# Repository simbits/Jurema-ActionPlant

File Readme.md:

Prototype for a new BioMachine
=====================

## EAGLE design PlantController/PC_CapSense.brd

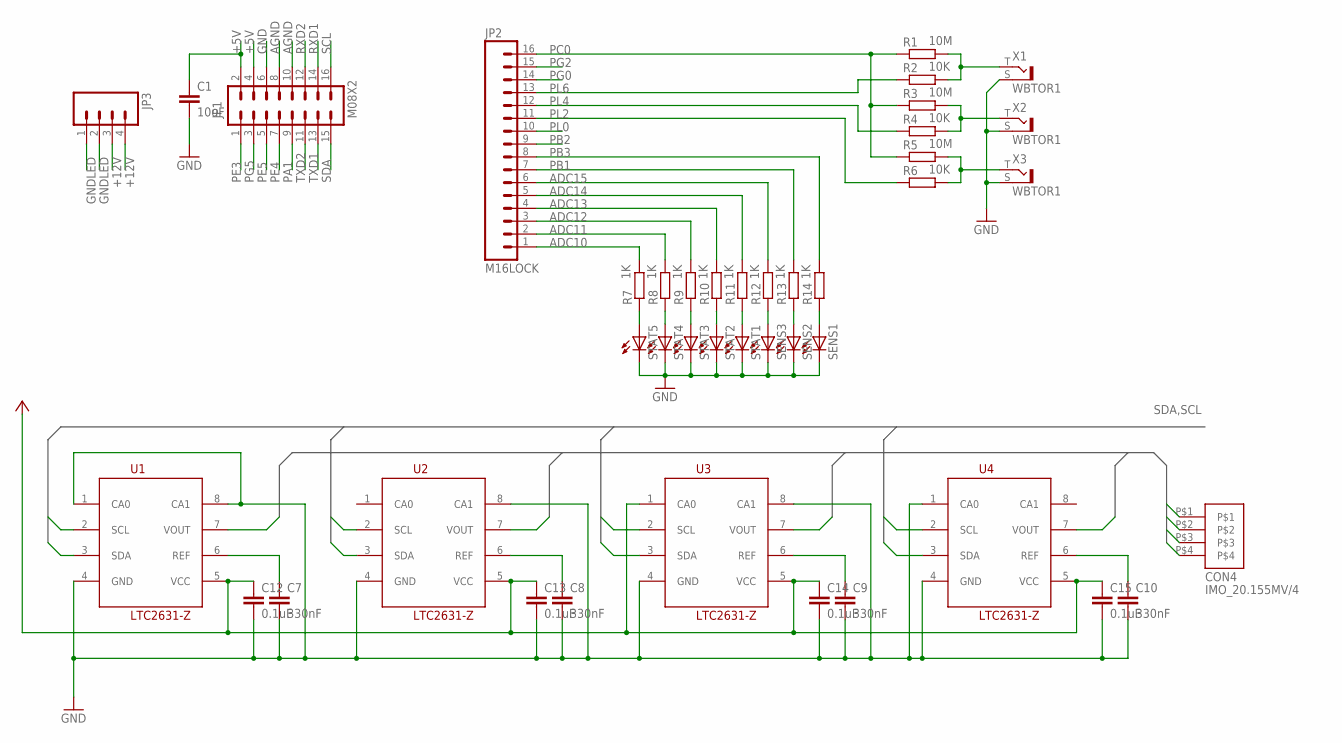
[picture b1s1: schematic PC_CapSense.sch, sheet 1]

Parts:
C1: 10uF; C0805
C7, C8, C9, C10: 330nF; C0805K
C12, C13, C14, C15: 0.1uF; C0805K
CON4: IMO_20.155MV/4
JP1: M08X2; 2X8
JP2: M16LOCK; 1X16_LOCK
JP3: M04LONGPADS; 1X04_LONGPADS
R1, R3, R5: 10M; M0805
R2, R4, R6: 10K; M0805
R7, R8, R9, R10, R11, R12, R13, R14: 1K; M0805
SENS1, SENS2, SENS3: LED3MM
STAT1, STAT2, STAT3, STAT4, STAT5: LED3MM
U1, U2, U3, U4: LTC2631-Z; TSOT23-8
X1, X2, X3: WBTOR1

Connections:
+5V: C1.1, C12.1, C13.1, C14.1, C15.1, JP1.2, JP1.4, U1.5 (VCC), U2.5 (VCC), U3.1 (CA0), U3.5 (VCC), U4.5 (VCC)
+12V: JP3.3, JP3.4
ADC10: JP2.1, R7.2
ADC11: JP2.2, R8.2
ADC12: JP2.3, R9.2
ADC13: JP2.4, R10.2
ADC14: JP2.5, R11.2
ADC15: JP2.6, R12.2
AGND: JP1.8, JP1.10, X1.S, X2.S, X3.S
GND: C1.2, C7.2, C8.2, C9.2, C10.2, C12.2, C13.2, C14.2, C15.2, JP1.6, U1.1 (CA0), U1.4 (GND), U1.8 (CA1), U2.4 (GND), U2.8 (CA1), U3.4 (GND), U3.8 (CA1), U4.1 (CA0), U4.4 (GND)
GNDLED: JP3.1, JP3.2, SENS1.K (C), SENS2.K (C), SENS3.K (C), STAT1.K (C), STAT2.K (C), STAT3.K (C), STAT4.K (C), STAT5.K (C)
unnamed: R1.2, R2.2, X1.T
unnamed: R3.2, R4.2, X2.T
unnamed: R5.2, R6.2, X3.T
unnamed: R7.1, STAT5.A
unnamed: R8.1, STAT4.A
unnamed: R9.1, STAT3.A
unnamed: R10.1, STAT2.A
unnamed: R11.1, STAT1.A
unnamed: R12.1, SENS3.A
unnamed: R13.1, SENS2.A
unnamed: R14.1, SENS1.A
unnamed: C10.1, U4.6 (REF)
unnamed: C9.1, U3.6 (REF)
unnamed: C8.1, U2.6 (REF)
unnamed: C7.1, U1.6 (REF)
PA1: JP1.9
PB1: JP2.7, R13.2
PB2: JP2.9
PB3: JP2.8, R14.2
PC0: JP2.16, R1.1, R3.1, R5.1
PE3: JP1.1
PE4: JP1.7
PE5: JP1.5
PG0: JP2.14
PG2: JP2.15
PG5: JP1.3
PL0: JP2.10
PL2: JP2.11, R6.1
PL4: JP2.12, R4.1
PL6: JP2.13, R2.1
RXD1: JP1.14
RXD2: JP1.12
SCL: JP1.16, U1.2 (SCL), U2.2 (SCL), U3.2 (SCL), U4.2 (SCL)
SDA: JP1.15, U1.3 (SDA), U2.3 (SDA), U3.3 (SDA), U4.3 (SDA)
TXD1: JP1.13
TXD2: JP1.11
VOUT0: CON4.P$1, U1.7 (VOUT)
VOUT1: CON4.P$2, U2.7 (VOUT)
VOUT2: CON4.P$3, U3.7 (VOUT)
VOUT3: CON4.P$4, U4.7 (VOUT)

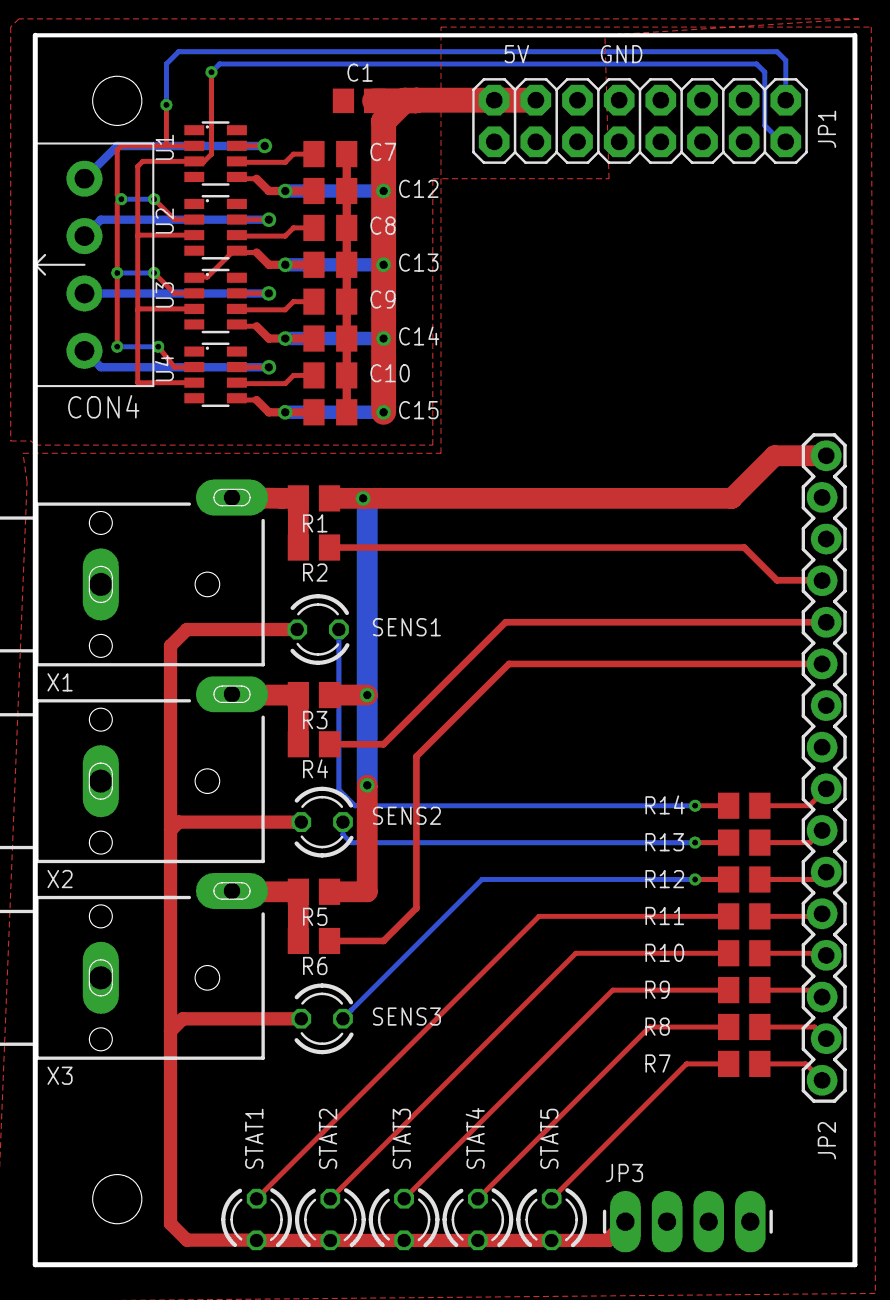
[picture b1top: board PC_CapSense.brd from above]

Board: 2 copper layers, 50.0 x 75.0 mm, 42 parts (0 on the bottom side), 38 nets.

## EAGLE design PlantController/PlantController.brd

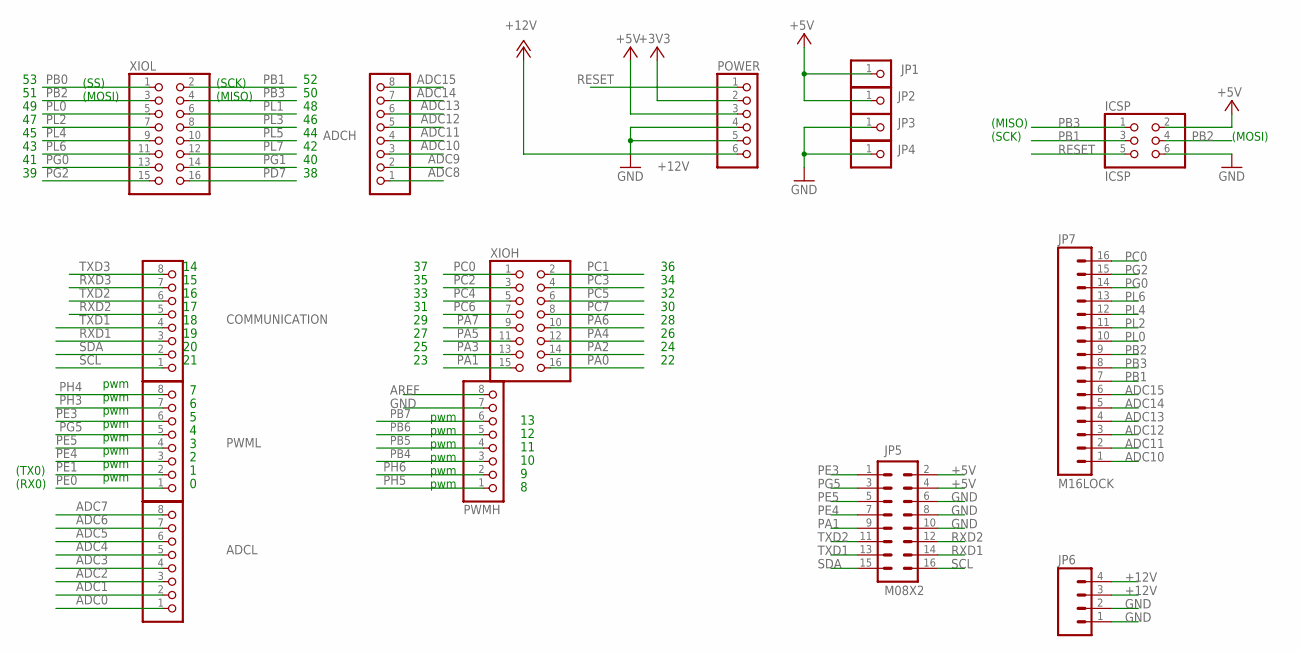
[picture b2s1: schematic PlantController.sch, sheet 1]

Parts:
ADCH: PINHD-1X8; 1X08
ADCL: PINHD-1X8; 1X08
COMMUNICATION: PINHD-1X8; 1X08
ICSP: ICSP; 2X03
JP1, JP2, JP3, JP4: PINHD-1X1; 1X01
JP5: M08X2; 2X8
JP6: M04LONGPADS; 1X04_LONGPADS
JP7: M16LOCK; 1X16_LOCK
POWER: PINHD-1X6; 1X06
PWMH: PINHD-1X8; 1X08
PWML: PINHD-1X8; 1X08
XIOH: PINHD-2X8; 2X08
XIOL: PINHD-2X8; 2X08

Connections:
+3V3: POWER.2
+5V: ICSP.2, JP1.1, JP2.1, JP5.2, JP5.4, POWER.3
+12V: JP6.3, JP6.4, POWER.6; also elsewhere on the board
ADC0: ADCL.1; also elsewhere on the board
ADC1: ADCL.2; also elsewhere on the board
ADC2: ADCL.3; also elsewhere on the board
ADC3: ADCL.4; also elsewhere on the board
ADC4: ADCL.5
ADC5: ADCL.6
ADC6: ADCL.7
ADC7: ADCL.8
ADC8: ADCH.1
ADC9: ADCH.2
ADC10: ADCH.3, JP7.1
ADC11: ADCH.4, JP7.2
ADC12: ADCH.5, JP7.3
ADC13: ADCH.6, JP7.4
ADC14: ADCH.7, JP7.5
ADC15: ADCH.8, JP7.6
AREF: PWMH.8
GND: ICSP.6, JP3.1, JP4.1, JP5.6, JP5.8, JP5.10, JP6.1, JP6.2, POWER.4, POWER.5, PWMH.7; also elsewhere on the board
PA0: XIOH.16
PA1: JP5.9, XIOH.15
PA2: XIOH.14
PA3: XIOH.13
PA4: XIOH.12
PA5: XIOH.11
PA6: XIOH.10
PA7: XIOH.9
PB0: XIOL.1
PB1: ICSP.3, JP7.7, XIOL.2
PB2: ICSP.4, JP7.9, XIOL.3
PB3: ICSP.1, JP7.8, XIOL.4
PB4: PWMH.3
PB5: PWMH.4
PB6: PWMH.5
PB7: PWMH.6
PC0: JP7.16, XIOH.1
PC1: XIOH.2
PC2: XIOH.3
PC3: XIOH.4
PC4: XIOH.5
PC5: XIOH.6
PC6: XIOH.7
PC7: XIOH.8
PD7: XIOL.16
PE0: PWML.1
PE1: PWML.2
PE3: JP5.1, PWML.6
PE4: JP5.7, PWML.3
PE5: JP5.5, PWML.4
PG0: JP7.14, XIOL.13
PG1: XIOL.14
PG2: JP7.15, XIOL.15
PG5: JP5.3, PWML.5
PH3: PWML.7
PH4: PWML.8
PH5: PWMH.1
PH6: PWMH.2
PL0: JP7.10, XIOL.5
PL1: XIOL.6
PL2: JP7.11, XIOL.7
PL3: XIOL.8
PL4: JP7.12, XIOL.9
PL5: XIOL.10
PL6: JP7.13, XIOL.11
PL7: XIOL.12
RESET: ICSP.5, POWER.1
RXD1: COMMUNICATION.3, JP5.14
RXD2: COMMUNICATION.5, JP5.12
RXD3: COMMUNICATION.7
SCL: COMMUNICATION.1, JP5.16
SDA: COMMUNICATION.2, JP5.15
TXD1: COMMUNICATION.4, JP5.13
TXD2: COMMUNICATION.6, JP5.11
TXD3: COMMUNICATION.8

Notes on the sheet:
(SCK)
(MISO)
(MOSI)
pwm
(TX0)
(RX0)
(SS)

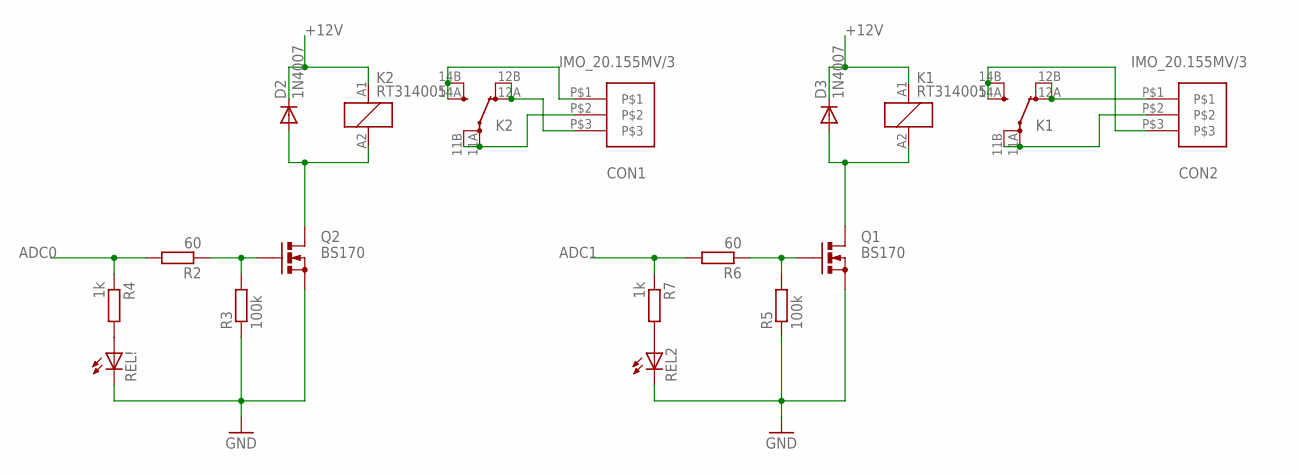
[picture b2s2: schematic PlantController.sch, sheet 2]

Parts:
CON1, CON2: IMO_20.155MV/3
D2, D3: 1N4007; DO41-10
K1, K2: RT314005; RT-C/O16A5
Q1, Q2: BS170; SOT54E
R2, R6: 60; R0805
R3, R5: 100k; R0805
R4, R7: 1k; R0805
REL2: LED5MM
REL!: LED5MM

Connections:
+12V: D2.C, D3.C, K1.A1 (1), K2.A1 (1); also elsewhere on the board
ADC0: R2.2, R4.1; also elsewhere on the board
ADC1: R6.2, R7.1; also elsewhere on the board
GND: Q1.S, Q2.S, R3.1, R5.1, REL2.K (C), REL!.K (C); also elsewhere on the board
unnamed: D2.A, K2.A2 (2), Q2.D
unnamed: Q2.G, R2.1, R3.2
unnamed: D3.A, K1.A2 (2), Q1.D
unnamed: R4.2, REL!.A
unnamed: Q1.G, R5.2, R6.1
unnamed: R7.2, REL2.A
unnamed: CON1.P$2, K2.11A (PA), K2.11B (PB)
unnamed: CON1.P$3, K2.12A (OA), K2.12B (OB)
unnamed: CON1.P$1, K2.14A (SA), K2.14B (SB)
unnamed: CON2.P$2, K1.11A (PA), K1.11B (PB)
unnamed: CON2.P$1, K1.12A (OA), K1.12B (OB)
unnamed: CON2.P$3, K1.14A (SA), K1.14B (SB)

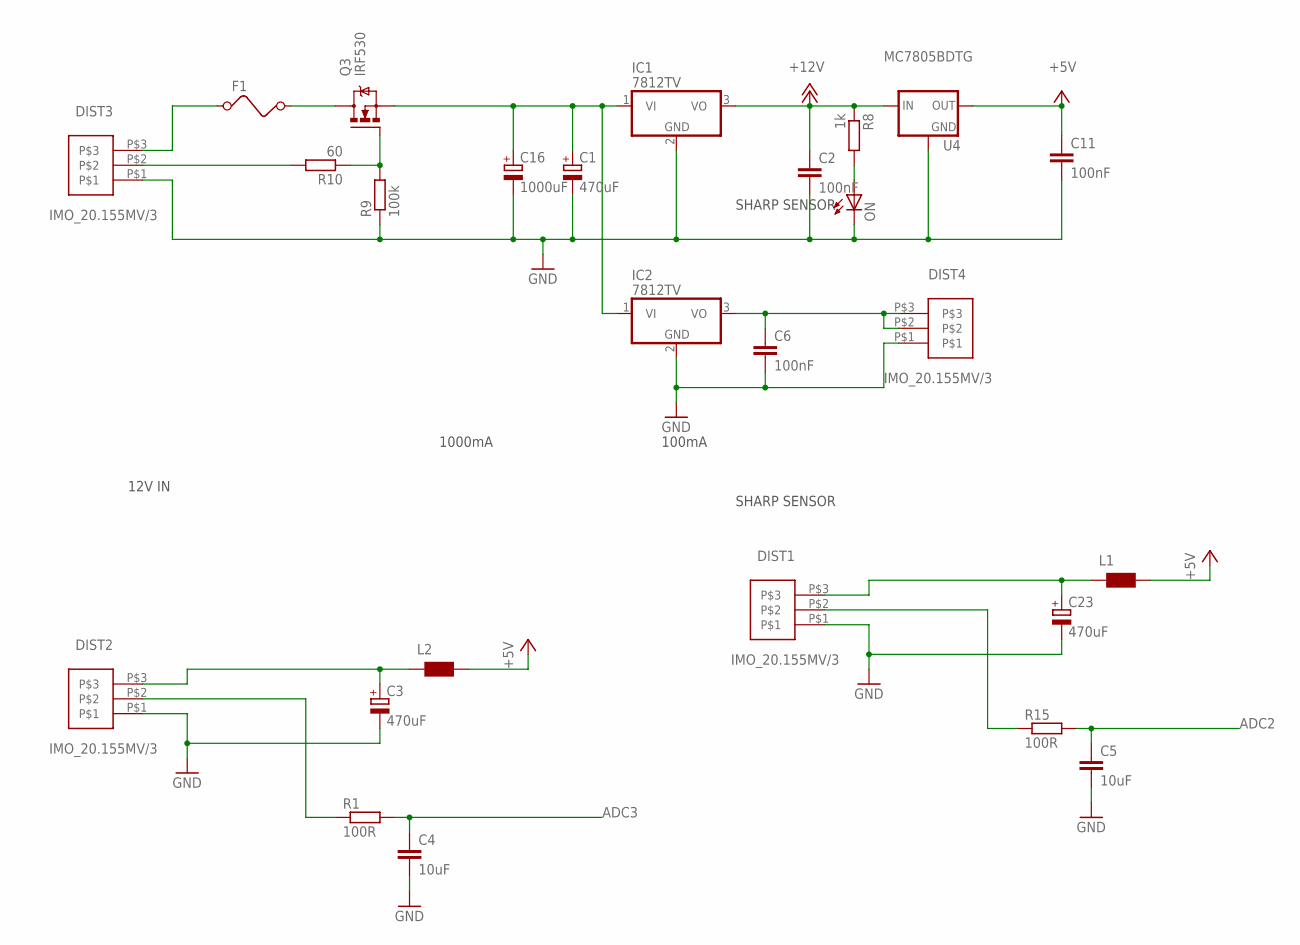
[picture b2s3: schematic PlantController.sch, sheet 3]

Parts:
C1: 470uF; E7,5-16
C2, C6, C11: 100nF; C0805K
C3, C23: 470uF; PANASONIC_F
C4, C5: 10uF; C0805K
C16: 1000uF; E7,5-16
DIST1, DIST2, DIST3, DIST4: IMO_20.155MV/3
F1: FUSE
IC1, IC2: 7812TV; TO220V
L1, L2: WE-KI_0805_B
ON: LED5MM
Q3: IRF530; TO220BV
R1, R15: 100R; R0805@1
R8: 1k; R0805
R9: 100k; R0805
R10: 60; R0805
U4: MC7805BDTG; DPAK

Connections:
+5V_SENS: C11.1, L1.1 (2), L2.1 (2), U4.3 (OUT)
+12V: C2.1, IC1.3 (VO), R8.1, U4.1 (IN); also elsewhere on the board
ADC2: C5.1, R15.2; also elsewhere on the board
ADC3: C4.1, R1.2; also elsewhere on the board
GND: C1.-, C2.2, C3.-, C4.2, C5.2, C6.2, C11.2, C16.-, C23.-, DIST1.P$1, DIST2.P$1, DIST3.P$1, DIST4.P$1, IC1.2 (GND), IC2.2 (GND), ON.K (C), R9.1, U4.4 (GND); also elsewhere on the board
unnamed: C6.1, DIST4.P$2, DIST4.P$3, IC2.3 (VO)
unnamed: Q3.G, R9.2, R10.1
unnamed: DIST3.P$2, R10.2
unnamed: ON.A, R8.2
SENSOR_POWER: C23.+, DIST1.P$3, L1.2 (1)
SENSOR_POWER1: C3.+, DIST2.P$3, L2.2 (1)
SHARP_SENSOR: DIST1.P$2, R15.1
SHARP_SENSOR1: DIST2.P$2, R1.1
VIN24: C1.+, C16.+, IC1.1 (VI), IC2.1 (VI), Q3.S
VINFIN: DIST3.P$3, F1.1
VINFOUT: F1.2, Q3.D

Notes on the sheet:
12V IN
1000mA
100mA
SHARP SENSOR

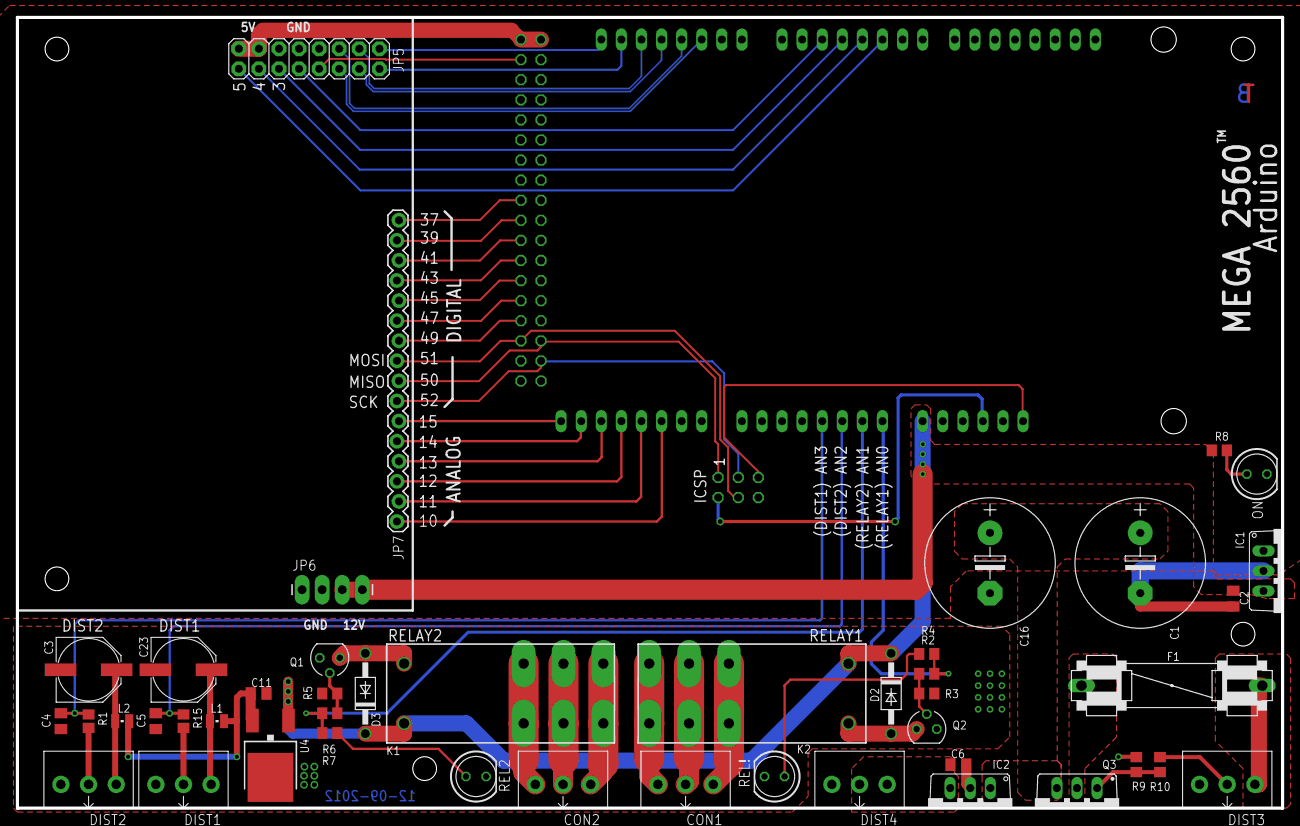
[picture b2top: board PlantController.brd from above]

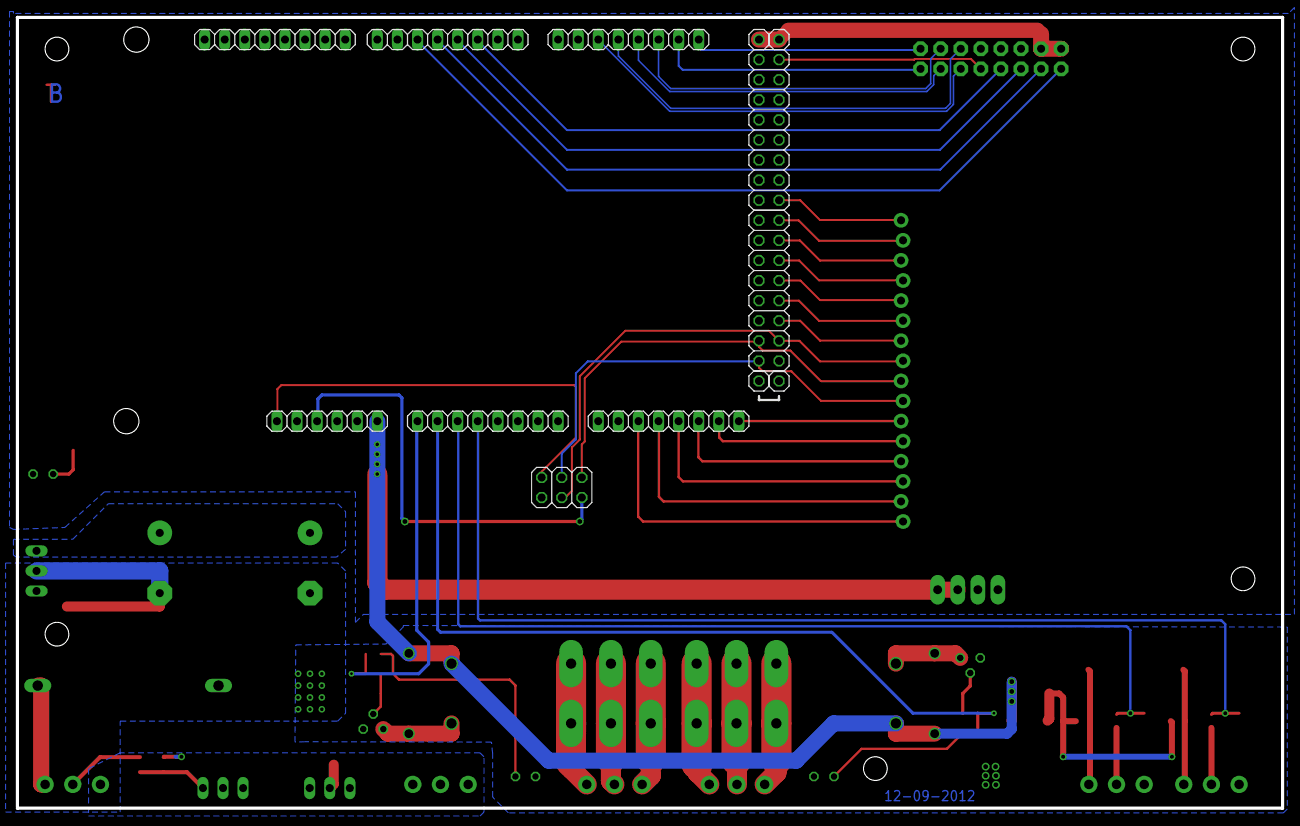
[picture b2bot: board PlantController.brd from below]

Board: 2 copper layers, 160.0 x 100.0 mm, 58 parts (13 on the bottom side), 59 nets.

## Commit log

2012-09-19 Initial commit
    Initial commit Jurema ActionPlant Development Edition
2012-09-19 Added Reamde
2013-06-20 * Added image files of schematic and board files

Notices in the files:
parts and their libraries:
SparkFun: Licensing: CC v3.0 Share-Alike You are welcome to use this library for commercial purposes.
